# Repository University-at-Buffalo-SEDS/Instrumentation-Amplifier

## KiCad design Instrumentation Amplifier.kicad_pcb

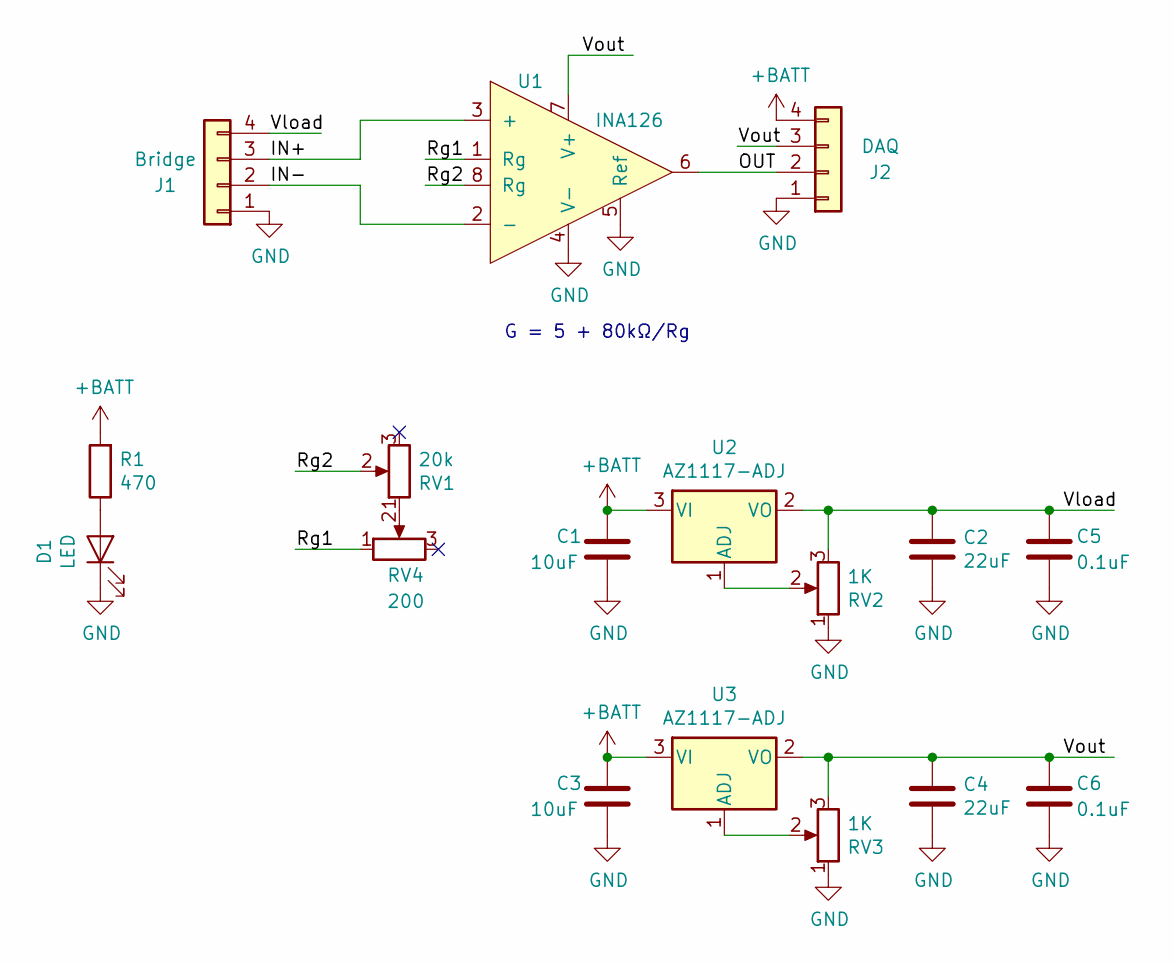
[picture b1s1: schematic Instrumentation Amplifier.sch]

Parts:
C1, C3: 10uF; C_Disc_D4.7mm_W2.5mm_P5.00mm
C2, C4: 22uF; C_Disc_D4.7mm_W2.5mm_P5.00mm
C5, C6: 0.1uF; C_0603_1608Metric_Pad1.05x0.95mm_HandSolder
D1: LED; LED_D3.0mm
J1: Bridge; TerminalBlock_bornier-4_P5.08mm
J2: DAQ; TerminalBlock_bornier-4_P5.08mm
R1: 470; R_Axial_DIN0207_L6.3mm_D2.5mm_P10.16mm_Horizontal
RV1: 20k; Bourns_PV36Y
RV2, RV3: 1K; Bourns_PV36W
RV4: 200; Bourns_PV36W
U1: INA126; SOIC-8_3.9x4.9mm_P1.27mm
U2, U3: AZ1117-ADJ; SOT-223-3_TabPin2

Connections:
+BATT: C1.1, C3.1, J2.4, R1.2, U2.3 (VI), U3.3 (VI)
/IN+: J1.3, U1.3 (+)
/IN-: J1.2, U1.2 (-)
/OUT: J2.2, U1.6
/Rg1: RV4.1, U1.1 (Rg)
/Rg2: RV1.2, U1.8 (Rg)
/Vload: C2.1, C5.1, J1.4, RV2.3, U2.2 (VO)
/Vout: C4.1, C6.1, J2.3, RV3.3, U1.7 (V+), U3.2 (VO)
GND: C1.2, C2.2, C3.2, C4.2, C5.2, C6.2, D1.1 (K), J1.1, J2.1, RV2.1, RV3.1, U1.4 (V-), U1.5 (Ref)
unnamed: D1.2 (A), R1.1
unnamed: RV1.1, RV4.2
unnamed: RV2.2, U2.1 (ADJ)
unnamed: RV3.2, U3.1 (ADJ)

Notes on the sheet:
G = 5 + 80kΩ/Rg

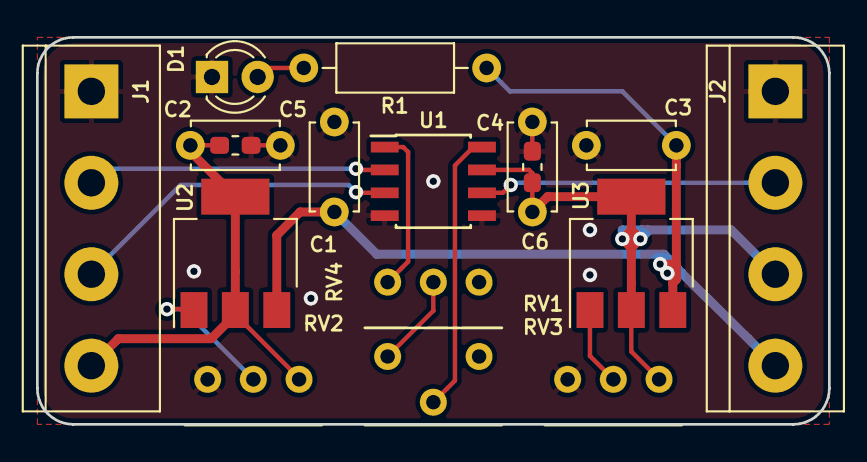
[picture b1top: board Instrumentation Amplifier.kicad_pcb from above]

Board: 2 copper layers, 44.0 x 21.5 mm, 17 parts (0 on the bottom side), 13 nets.

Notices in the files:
Instrumentation Amplifier.kicad_pcb:
© 2019 Owen Torres
